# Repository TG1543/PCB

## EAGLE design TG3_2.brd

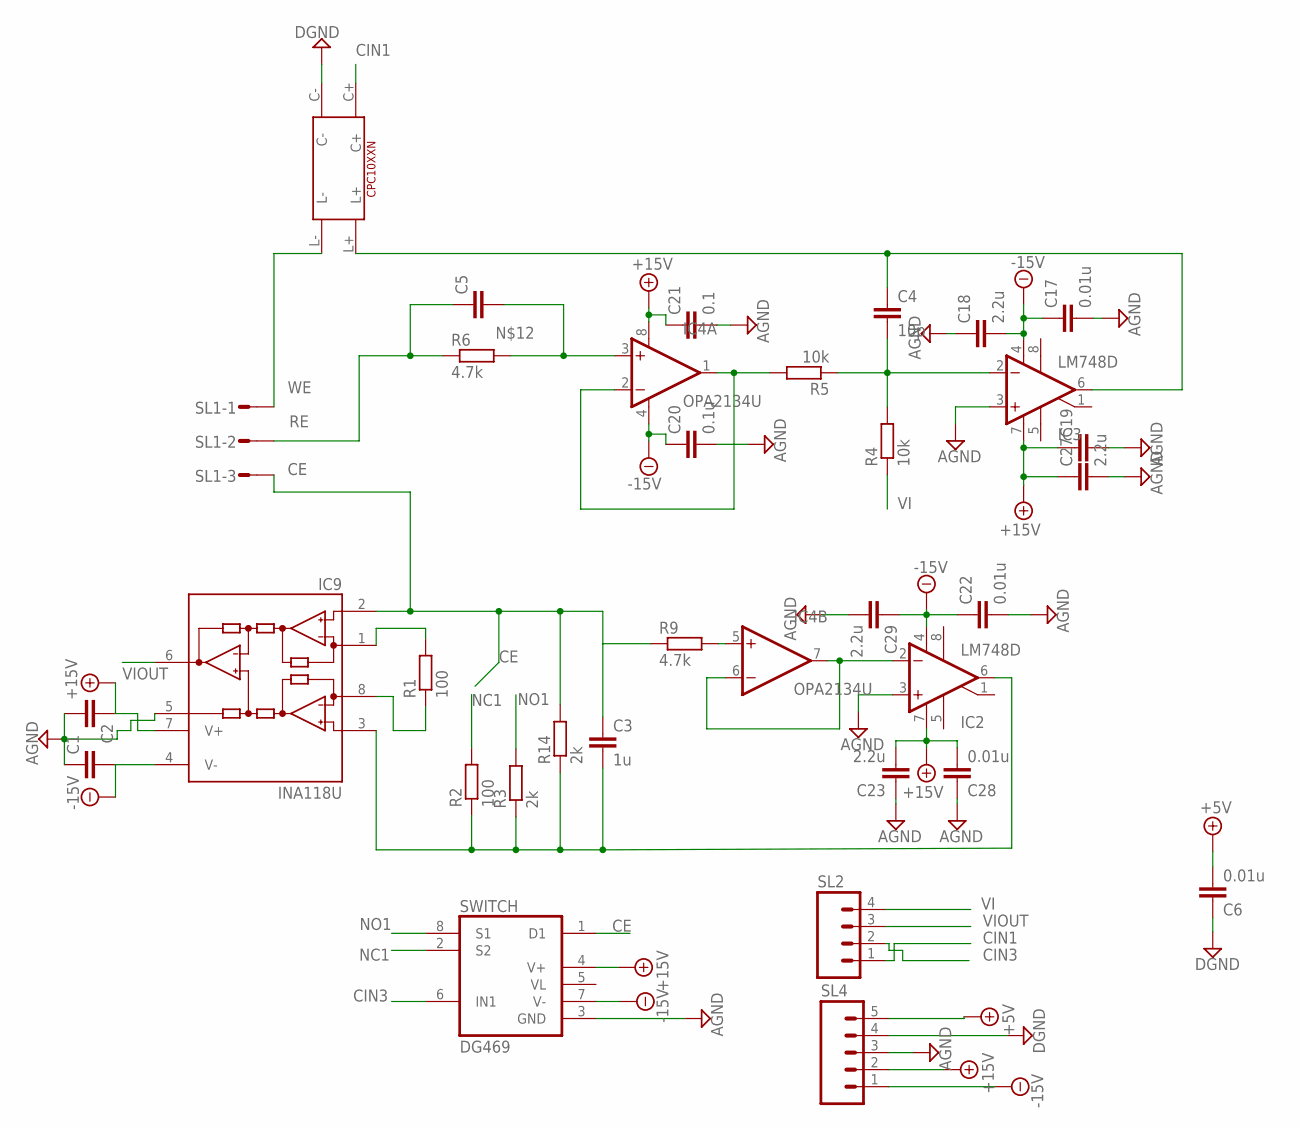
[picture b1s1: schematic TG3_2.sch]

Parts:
C1, C2, C5, C19: C; C0805
C3: 1u; C0805
C4: 10p; C0805
C6, C17, C22, C28: 0.01u; C0805
C18, C23, C27, C29: 2.2u; C0805
C20: 0.1u; C0805
C21: 0.1; C0805
IC2, IC3: LM748D; SO08
IC4: OPA2134U; SO08
IC9: INA118U; SO08
R1, R2: 100; R0805
R3, R14: 2k; R0805
R4, R5: 10k; R0805
R6, R9: 4.7k; R0805
SL1: M03S; 03P
SL2: M04; 04P
SL4: M05; 05P
SWITCH: DG469; SO08
U$5: CPC10XXN

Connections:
+5V: C6.2, SL4.5
+15V: C2.1, C19.1, C21.1, C23.2, C27.1, C28.2, IC2.7 (V+), IC3.7 (V+), IC4.8 (V+), IC9.7 (V+), SL4.2, SWITCH.4 (V+)
-15V: C1.2, C17.1, C18.2, C20.1, C22.1, C29.1, IC2.4 (V-), IC3.4 (V-), IC4.4 (V-), IC9.4 (V-), SL4.1, SWITCH.7 (V-)
AGND: C1.1, C2.2, C17.2, C18.1, C19.2, C20.2, C21.2, C22.2, C23.1, C27.2, C28.1, C29.2, IC2.3 (+IN), IC3.3 (+IN), IC9.5 (REF), SL4.3, SWITCH.3 (GND)
CE: C3.1, IC9.2 (-IN), R9.1, R14.2, SL1.3, SWITCH.1 (D1)
CIN1: SL2.1, U$5.C+
CIN3: SL2.2, SWITCH.6 (IN1)
DGND: C6.1, SL4.4, U$5.C-
unnamed: IC9.8 (RG), R1.1
unnamed: C3.2, IC2.6 (OUT), IC9.3 (+IN), R2.1, R3.1, R14.1
unnamed: IC9.1 (RG), R1.2
unnamed: IC4.1 (OUT), IC4.2 (-IN), R5.2
unnamed: C4.2, IC3.2 (-IN), R4.2, R5.1
unnamed: C5.2, IC4.3 (+IN), R6.2
unnamed: IC2.2 (-IN), IC4.6 (-IN), IC4.7 (OUT)
unnamed: IC4.5 (+IN), R9.2
unnamed: C4.1, IC3.6 (OUT), U$5.L+
NC1: R2.2, SWITCH.2 (S2)
NO1: R3.2, SWITCH.8 (S1)
RE: C5.1, R6.1, SL1.2
VI: R4.1, SL2.4
VIOUT: IC9.6 (OUT), SL2.3
VL: SWITCH.5 (VL)
WE: SL1.1, U$5.L-

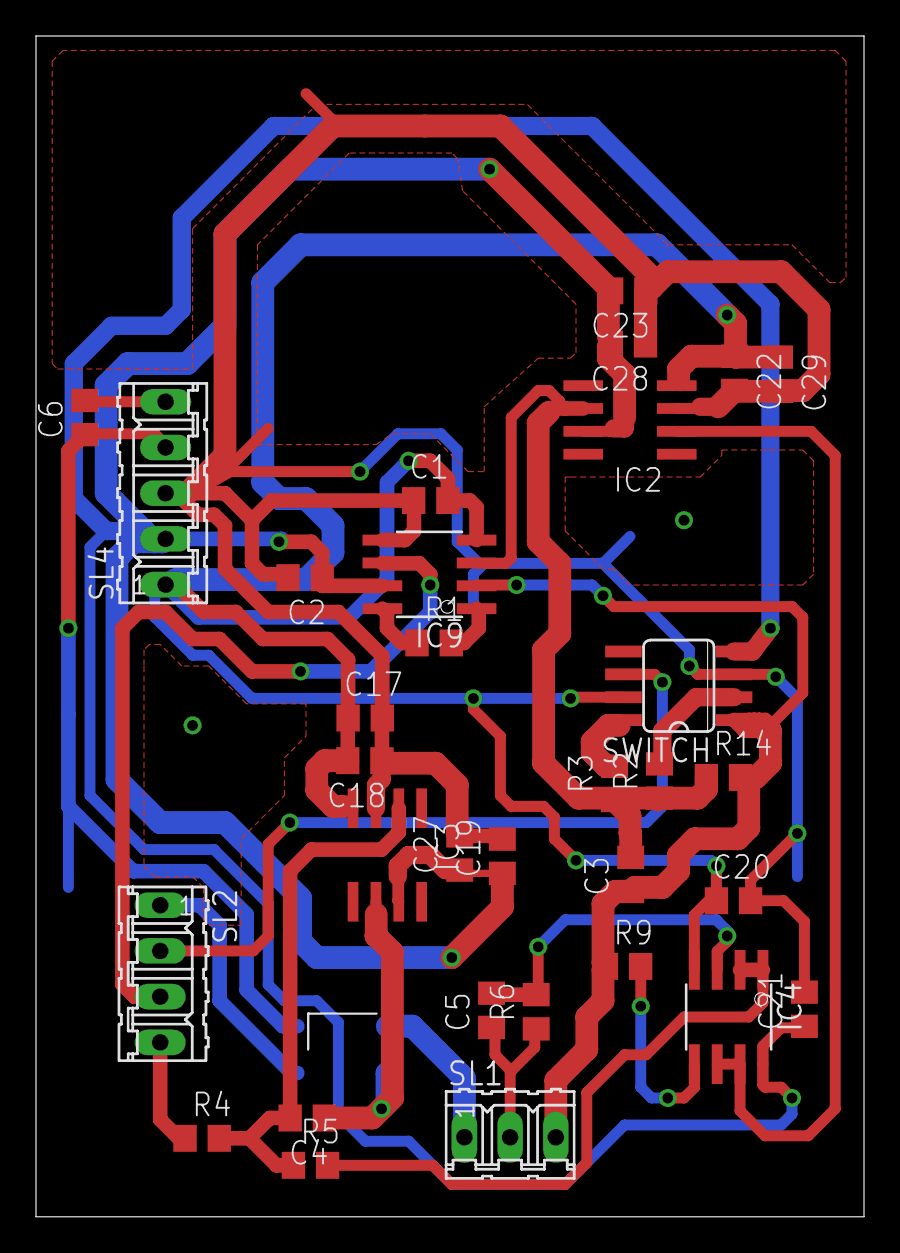
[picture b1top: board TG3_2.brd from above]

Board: 2 copper layers, 46.0 x 65.6 mm, 33 parts (1 on the bottom side), 23 nets.

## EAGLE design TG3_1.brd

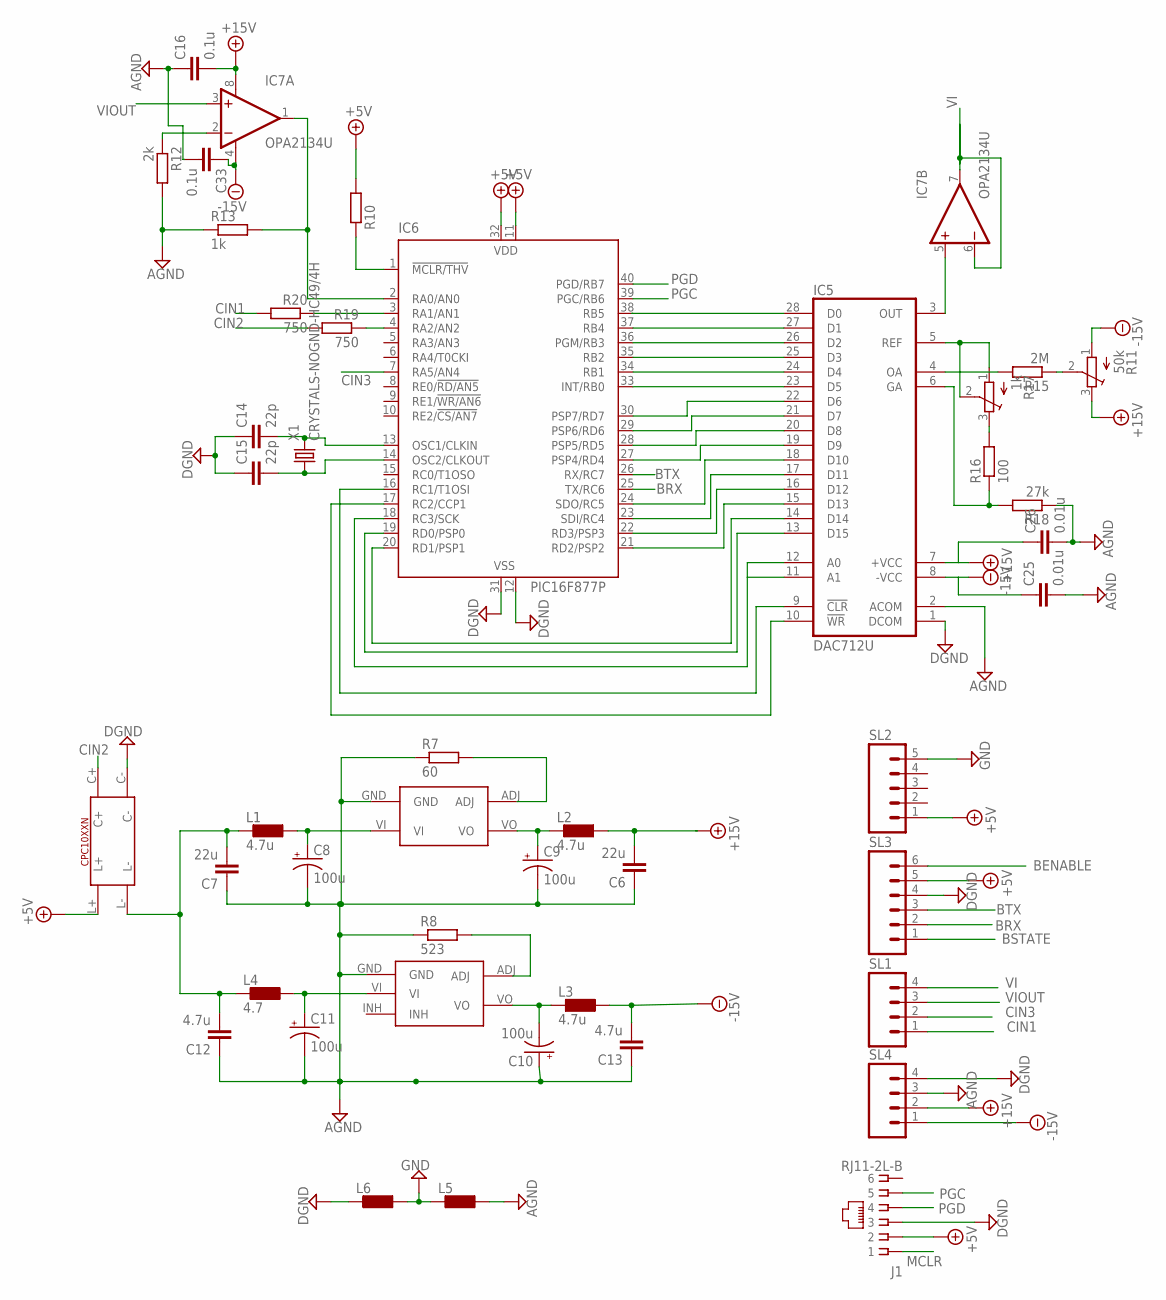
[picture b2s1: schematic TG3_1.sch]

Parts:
C6, C7: 22u; C0805
C8, C9, C10, C11: 100u; 150CLZ-0810
C12, C13: 4.7u; C0805
C14, C15: 22p; C0805
C16, C33: 0.1u; C0805
C25, C26: 0.01u; C0805
IC5: DAC712U; SO28-3
IC6: PIC16F877P; DIL40
IC7: OPA2134U; SO08
J1: RJ11-2L-B; RJ11-NO_SHIELD
L1, L2, L3: 4.7u; L2012C
L4: 4.7; L2012C
L5, L6: LL2012C; L2012C
R7: 60; R0805
R8: 523; R0805
R10: R; R0805
R11: 50k; 3223W
R12: 2k; R0805
R13: 1k; R0805
R15: 2M; R0805
R16: 100; R0805
R17: 1k; 3223W
R18: 27k; R0805
R19, R20: 750; R0805
SL1, SL4: M04; 04P
SL2: M05; 05P
SL3: M06; 06P
U$1: PTN04050C
U$2: PTN04050A
U$6: CPC10XXN
X1: CRYSTALS-NOGND-HC49/4H; HC49

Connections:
+5V: IC6.11 (VDD), IC6.32 (VDD), J1.2, R10.2, SL2.1, SL3.5, U$6.L+
+15V: C6.2, C16.2, C26.1, IC5.7 (+VCC), IC7.8 (V+), L2.1, R11.3 (E), SL4.2
-15V: C13.2, C25.1, C33.1, IC5.8 (-VCC), IC7.4 (V-), L3.1, R11.1 (A), SL4.1
AGND: C6.1, C7.1, C8.-, C9.-, C10.+, C11.-, C12.1, C13.1, C16.1, C25.2, C26.2, C33.2, IC5.2 (ACOM), L5.1, R7.1, R8.1, R12.2, R13.1, R18.1, SL4.3, U$1.GND, U$2.GND
BENABLE: SL3.6
BRX: IC6.25 (TX/RC6), SL3.2
BSTATE: SL3.1
BTX: IC6.26 (RX/RC7), SL3.3
CIN1: R20.2, SL1.1
CIN2: R19.2, U$6.C+
CIN3: IC6.7 (RA5/AN4), SL1.2
DGND: C14.1, C15.1, IC5.1 (DCOM), IC6.12 (VSS), IC6.31 (VSS), J1.3, L6.2, SL3.4, SL4.4, U$6.C-
GND: L5.2, L6.1, SL2.5
MCLR: IC6.1 (!MCLR/THV), J1.1, R10.1
unnamed: IC5.21 (D7), IC6.29 (PSP6/RD6)
unnamed: R7.2, U$1.ADJ
unnamed: IC5.22 (D6), IC6.30 (PSP7/RD7)
unnamed: C9.+, L2.2, U$1.VO
unnamed: IC5.23 (D5), IC6.33 (INT/RB0)
unnamed: C8.+, L1.1, U$1.VI
unnamed: C14.2, IC6.13 (OSC1/CLKIN), X1.2
unnamed: C15.2, IC6.14 (OSC2/CLKOUT), X1.1
unnamed: C11.+, L4.1, U$2.VI
unnamed: IC5.24 (D4), IC6.34 (RB1)
unnamed: IC5.25 (D3), IC6.35 (RB2)
unnamed: IC5.26 (D2), IC6.36 (PGM/RB3)
unnamed: C10.-, L3.2, U$2.VO
unnamed: R8.2, U$2.ADJ
unnamed: IC6.3 (RA1/AN1), R20.1
unnamed: IC5.3 (OUT), IC7.5 (+IN)
unnamed: IC6.4 (RA2/AN2), R19.1
unnamed: IC7.2 (-IN), R12.1
unnamed: IC5.27 (D1), IC6.37 (RB4)
unnamed: IC5.20 (D8), IC6.28 (PSP5/RD5)
unnamed: IC5.19 (D9), IC6.27 (PSP4/RD4)
unnamed: IC5.18 (D10), IC6.24 (SDO/RC5)
unnamed: IC5.17 (D11), IC6.23 (SDI/RC4)
unnamed: IC5.16 (D12), IC6.22 (RD3/PSP3)
unnamed: IC5.15 (D13), IC6.21 (RD2/PSP2)
unnamed: IC5.14 (D14), IC6.20 (RD1/PSP1)
unnamed: IC5.13 (D15), IC6.19 (RD0/PSP0)
unnamed: IC5.11 (A1), IC5.12 (A0), IC6.18 (RC3/SCK)
unnamed: C7.2, C12.2, L1.2, L4.2, U$6.L-
unnamed: IC5.9 (!CLR), IC6.16 (RC1/T1OSI)
unnamed: IC5.10 (!WR), IC6.17 (RC2/CCP1)
unnamed: R11.2 (S), R15.1
unnamed: IC5.4 (OA), R15.2
unnamed: IC5.5 (REF), R17.1 (A), R17.2 (S)
unnamed: R16.2, R17.3 (E)
unnamed: IC5.6 (GA), R16.1, R18.2
PGC: IC6.39 (PGC/RB6), J1.5
PGD: IC6.40 (PGD/RB7), J1.4
VI: IC7.6 (-IN), IC7.7 (OUT), SL1.4
VIOUT: IC7.3 (+IN), SL1.3
VIOUT_IN: IC6.2 (RA0/AN0), IC7.1 (OUT), R13.2

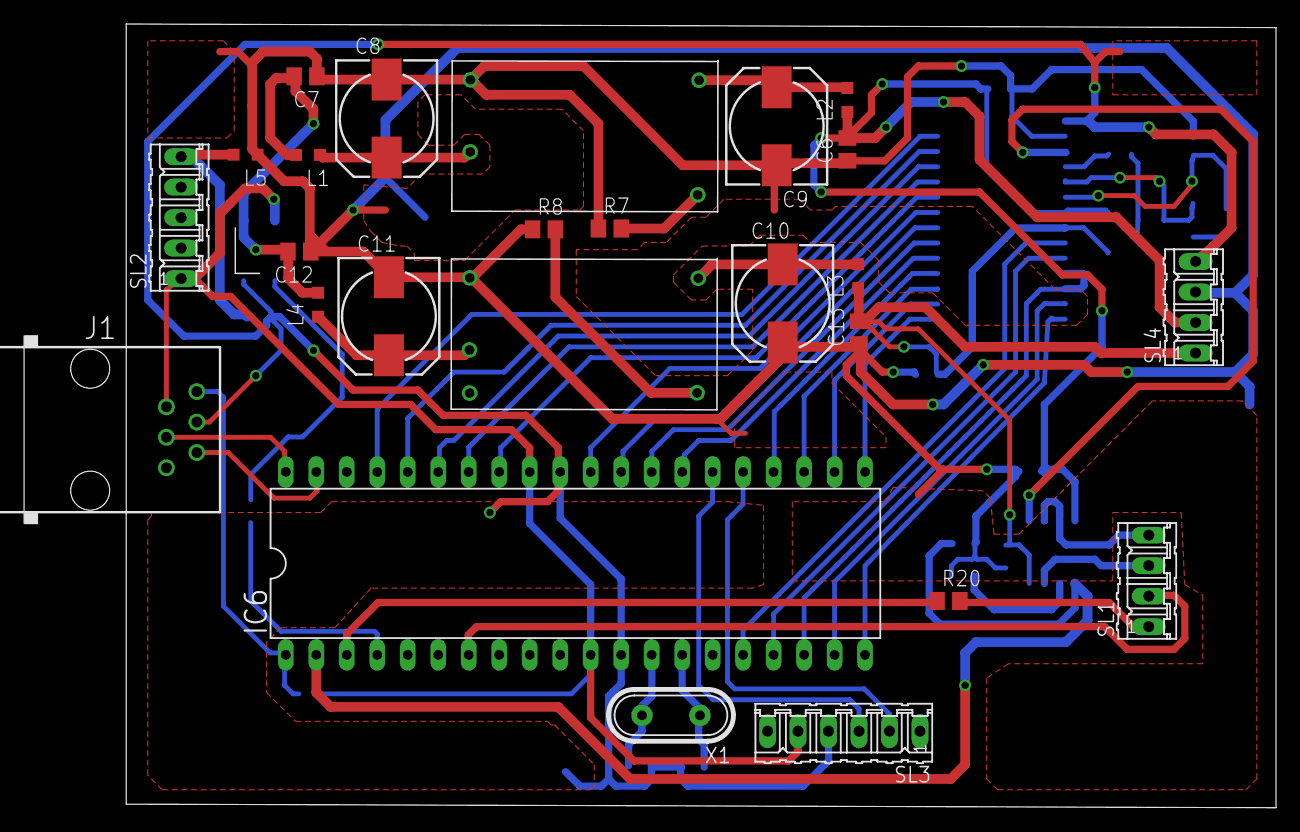
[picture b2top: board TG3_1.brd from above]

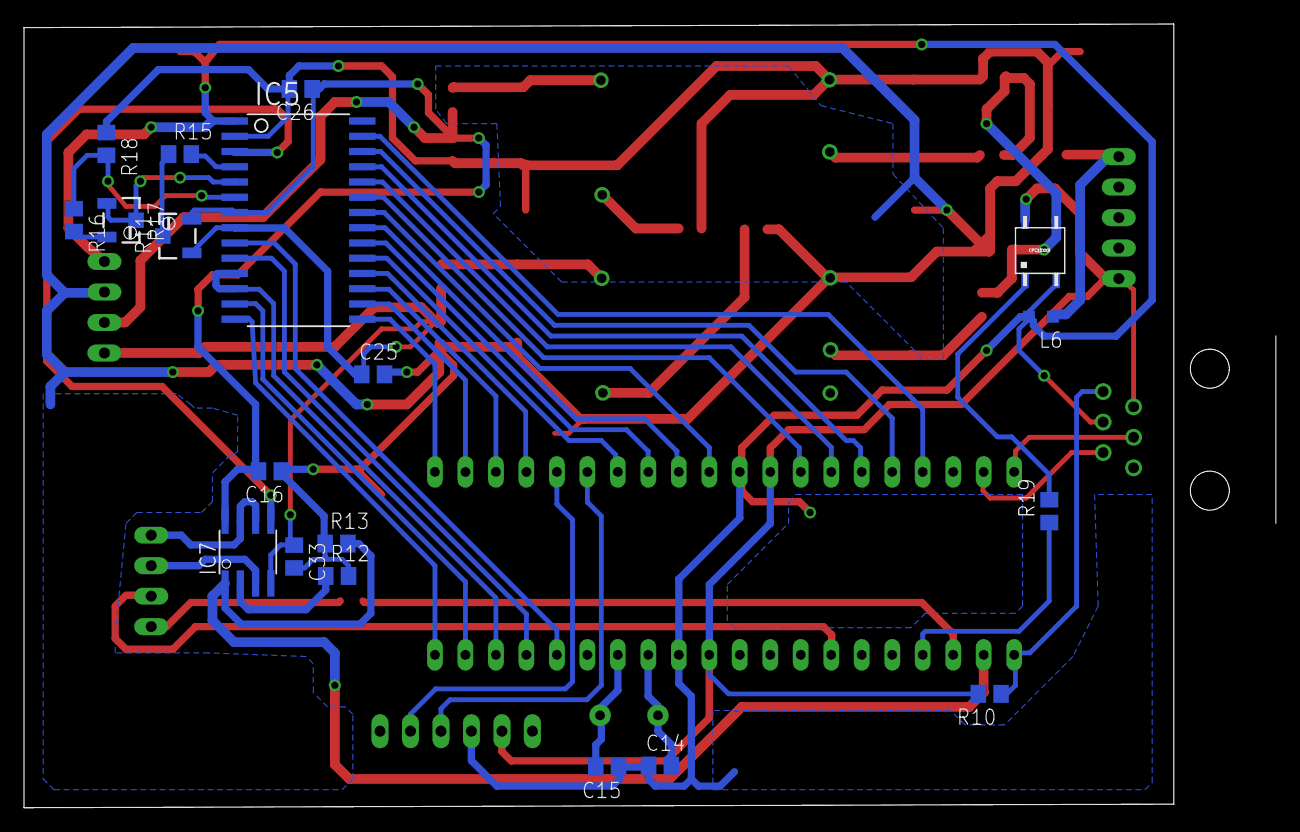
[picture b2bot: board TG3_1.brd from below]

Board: 2 copper layers, 104.3 x 65.3 mm, 44 parts (19 on the bottom side), 53 nets.
